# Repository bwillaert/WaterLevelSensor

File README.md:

# WaterLevelSensor
Capacitive water level sensor

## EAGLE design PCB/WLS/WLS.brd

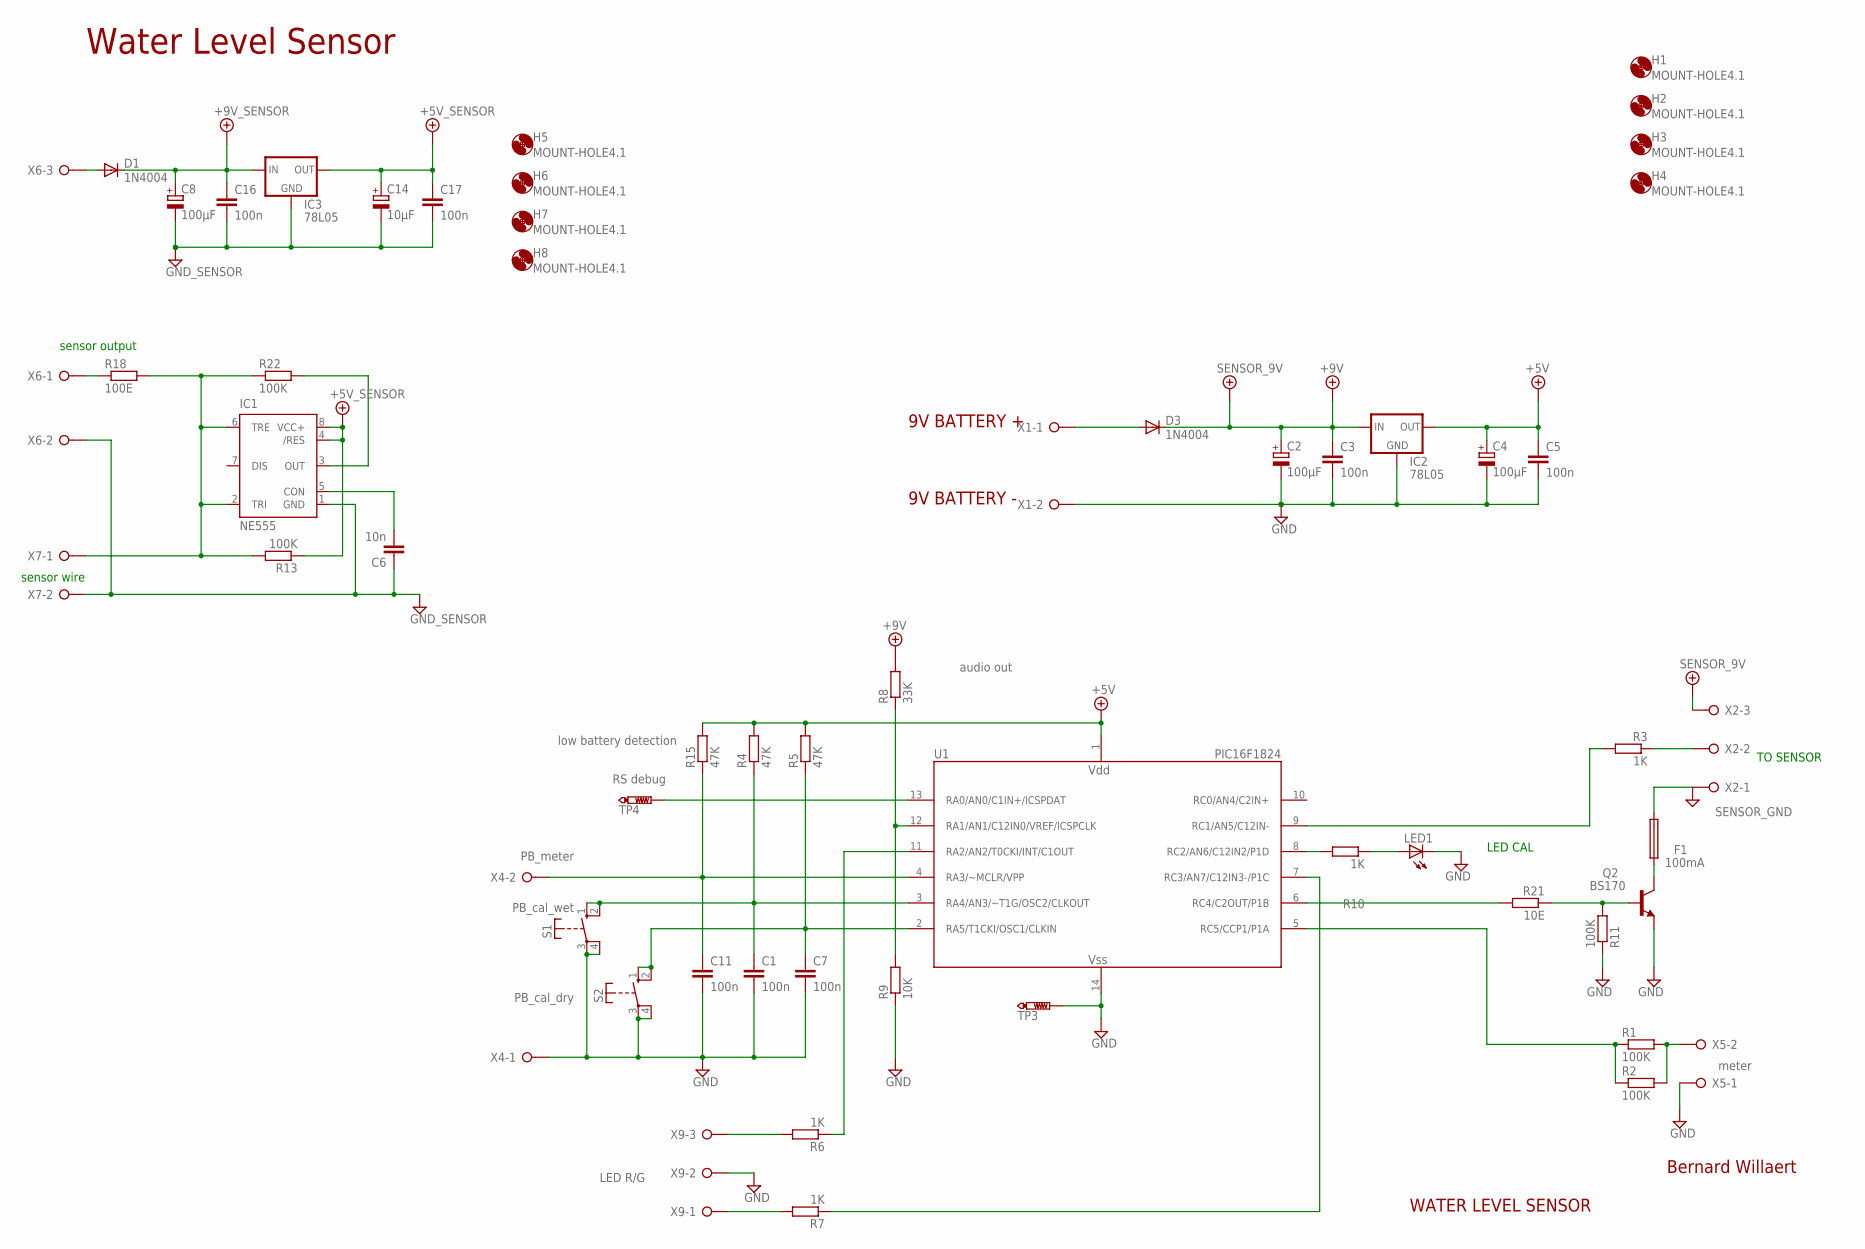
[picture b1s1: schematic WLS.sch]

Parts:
C1, C3, C5, C7, C11, C16, C17: 100n; C050-025X075
C2, C4, C8: 100µF; E5-6
C6: 10n; C050-025X075
C14: 10µF; E5-6
D1, D3: 1N4004; DO41-10
F1: 100mA; TR5
H1, H2, H3, H4, H5, H6, H7, H8: MOUNT-HOLE4.1; 4,1
IC1: NE555; DIL-08
IC2, IC3: 78L05; 78LXX
LED1: LED3MM
Q2: BS170; TO92-CBE
R1, R2, R11, R13, R22: 100K; 0207/10
R3, R6, R7, R10: 1K; 0207/10
R4, R5, R15: 47K; 0207/10
R8: 33K; 0207/10
R9: 10K; 0207/10
R18: 100E; 0207/10
R21: 10E; 0207/10
S1, S2: DTE6K
TP3, TP4: PTR1PAD1-17; P1-17
U1: PIC16F1824; DIP-14
X1, X4, X5, X7: W237-02P; W237-132
X2, X6, X9: W237-3E

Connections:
+5V: C4.+, C5.1, C14.+, C17.1, IC2.OUT, IC3.OUT, R4.2, R5.2, R15.2, U1.1 (VDD)
+12V: C2.+, C3.1, C8.+, C16.1, D1.C, D3.C, IC1.4 (/RES), IC1.8 (VCC+), IC2.IN, IC3.IN, R8.2, R13.1, X2.3
GND: C2.-, C3.2, C4.-, C5.2, C6.1, C8.-, C14.-, C16.2, C17.2, F1.2, IC1.1 (GND), IC2.GND, IC3.GND, LED1.K (C), Q2.E, R9.1, R11.1, TP3.TP, U1.14 (VSS), X1.2, X2.1, X5.1, X6.2, X7.2, X9.2
unnamed: IC1.2 (TRI), IC1.6 (TRE), R13.2, R18.2, R22.1, X7.1
unnamed: R21.2, U1.6 (RC4/C2OUT/P1B)
unnamed: IC1.3 (OUT), R22.2
unnamed: C1.1, R4.1, S1.1 (S), S1.2 (S), U1.3 (RA4/AN3/~T1G/OSC2/CLKOUT)
unnamed: R3.1, X2.2
unnamed: R3.2, U1.9 (RC1/AN5/C12IN-)
unnamed: R6.2, X9.3
unnamed: R7.2, X9.1
unnamed: R7.1, U1.7 (RC3/AN7/C12IN3-/P1C)
unnamed: C11.1, R15.1, U1.4 (RA3/~MCLR/VPP), X4.2
unnamed: R6.1, U1.11 (RA2/AN2/T0CKI/INT/C1OUT)
unnamed: C6.2, IC1.5 (CON)
unnamed: R10.2, U1.8 (RC2/AN6/C12IN2/P1D)
unnamed: R18.1, X6.1
unnamed: R1.1, R2.1, U1.5 (RC5/CCP1/P1A)
unnamed: R1.2, R2.2, X5.2
unnamed: R8.1, R9.2, U1.12 (RA1/AN1/C12IN0/VREF/ICSPCLK)
unnamed: Q2.B, R11.2, R21.1
unnamed: D1.A, X6.3
unnamed: TP4.TP, U1.13 (RA0/AN0/C1IN+/ICSPDAT)
unnamed: LED1.A, R10.1
unnamed: F1.1, Q2.C
unnamed: C1.2, C7.2, C11.2, S1.3, S1.4, S2.3, S2.4, X4.1
unnamed: C7.1, R5.1, S2.1 (S), S2.2 (S), U1.2 (RA5/T1CKI/OSC1/CLKIN)
unnamed: D3.A, X1.1

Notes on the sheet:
Water Level Sensor
low battery detection
WATER LEVEL SENSOR
Bernard Willaert
9V BATTERY +
9V BATTERY -
PB_meter
meter
audio out
sensor wire
sensor output
RS debug
TO SENSOR
PB_cal_wet
PB_cal_dry
LED R/G
LED CAL

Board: 2 copper layers, 56 parts (0 on the bottom side), 28 nets, no tracks yet.

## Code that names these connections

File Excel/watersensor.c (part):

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
    // INPUT    ===> The PORTA pins can be configured to operate as Interrupt-on-Change (IOC) pins.
    // p 141 datasheet  --- 13.2   Individual Pin Configuration  --> PORT A falling edge = PB press
    PB_METER_WATER          RA3 = pin 4
    PB_CAL_WET                     RA5 = pin 2
    PB_CAL_DRY                     RA4 = pin 3
    SENSOR_IN                       RC1 = pin 9           // IN AN comparator 2
    BATTERY_IN                      RC0 = pin 10        // ADC4 
  
    // OUTPUT
    SENSOR_POWER_OUT                      -------------- >LATA.LATA2
    METER_PWM_OUT           RC5 = pin 5  PWM1
    LED_CAL_OUT
    LED_RED_OUT   
    LED_GREEN_OUT
    DEBUG_RS_OUT                RA0 = pin 13
    
    COMP2_OUT                       RC4 = pin 6
*/

 // EEPROM locations
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    // GPIO init
    // PORT A
    TRISA.TRISA0 = OUT;  // PIN 13
    PORTA.RA0 = 1;
    TRISA.TRISA1 = OUT;   // PIN 12
    PORTA.RA1 = 1;
    TRISA.TRISA2 = OUT;  // PIN 11
    PORTA.RA2 = 1;
    TRISA.TRISA3 = OUT;  // PIN 4
    PORTA.RA3 = 1;
    TRISA.TRISA4 = IN;   // PIN 3
    PORTA.RA4 = 1;
    TRISA.TRISA5 = OUT;  // PIN 2
    PORTA.RA5 = 1;

    // PORT C
    TRISC.TRISC0 = IN;  // PIN 10 battery in
    PORTC.RC0 = 1;
    TRISC.TRISC1 = IN;  // PIN 9 = comparator in
    PORTC.RC1 = 1;
    TRISC.TRISC2 = OUT;  // PIN 8 
    PORTC.RC2 = 1;
    TRISC.TRISC3 = OUT;  // PIN 7
    PORTC.RC3 = 1;
    TRISC.TRISC4 = OUT; // PIN 6 
    PORTC.RC4 = 1;
    TRISC.TRISC5 = OUT; // PIN 5  PWM1
    PORTC.RC5 = 1;

    // Analog input pins
    ANSELC.ANSC0 = 1;     // battery in
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    OPTION_REG.TMR0CS = 0;  // FOSC / 4   --> 8 MHz
    INTCON.TMR0IE = 1;          // timer0 interrupt enable

   // PWM1 - RC5 - pin5
   PWM1_Init(250000);          // 250 kHz
   PWM1_Set_Duty(0);  
   PWM1_Start();
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
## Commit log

2021-08-24 WLS repo created
2021-08-24 WLS init
2021-08-24 Init
2021-08-24 Added WLS1
2021-08-24 Dev start
2022-05-05 Initial rework
2023-05-29 WaterLevelSensor repo init
2023-06-13 Updated PCB sensor
2023-09-03 Added WLS4 and WLS5
2023-09-22 Averaging the current sensor value
2023-12-21 Added manual
2023-12-21 Added arduino_for_dummies
2023-12-21 Added datasheet
